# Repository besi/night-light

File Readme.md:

# NightLight

A simple night light to defy the nightly demons.

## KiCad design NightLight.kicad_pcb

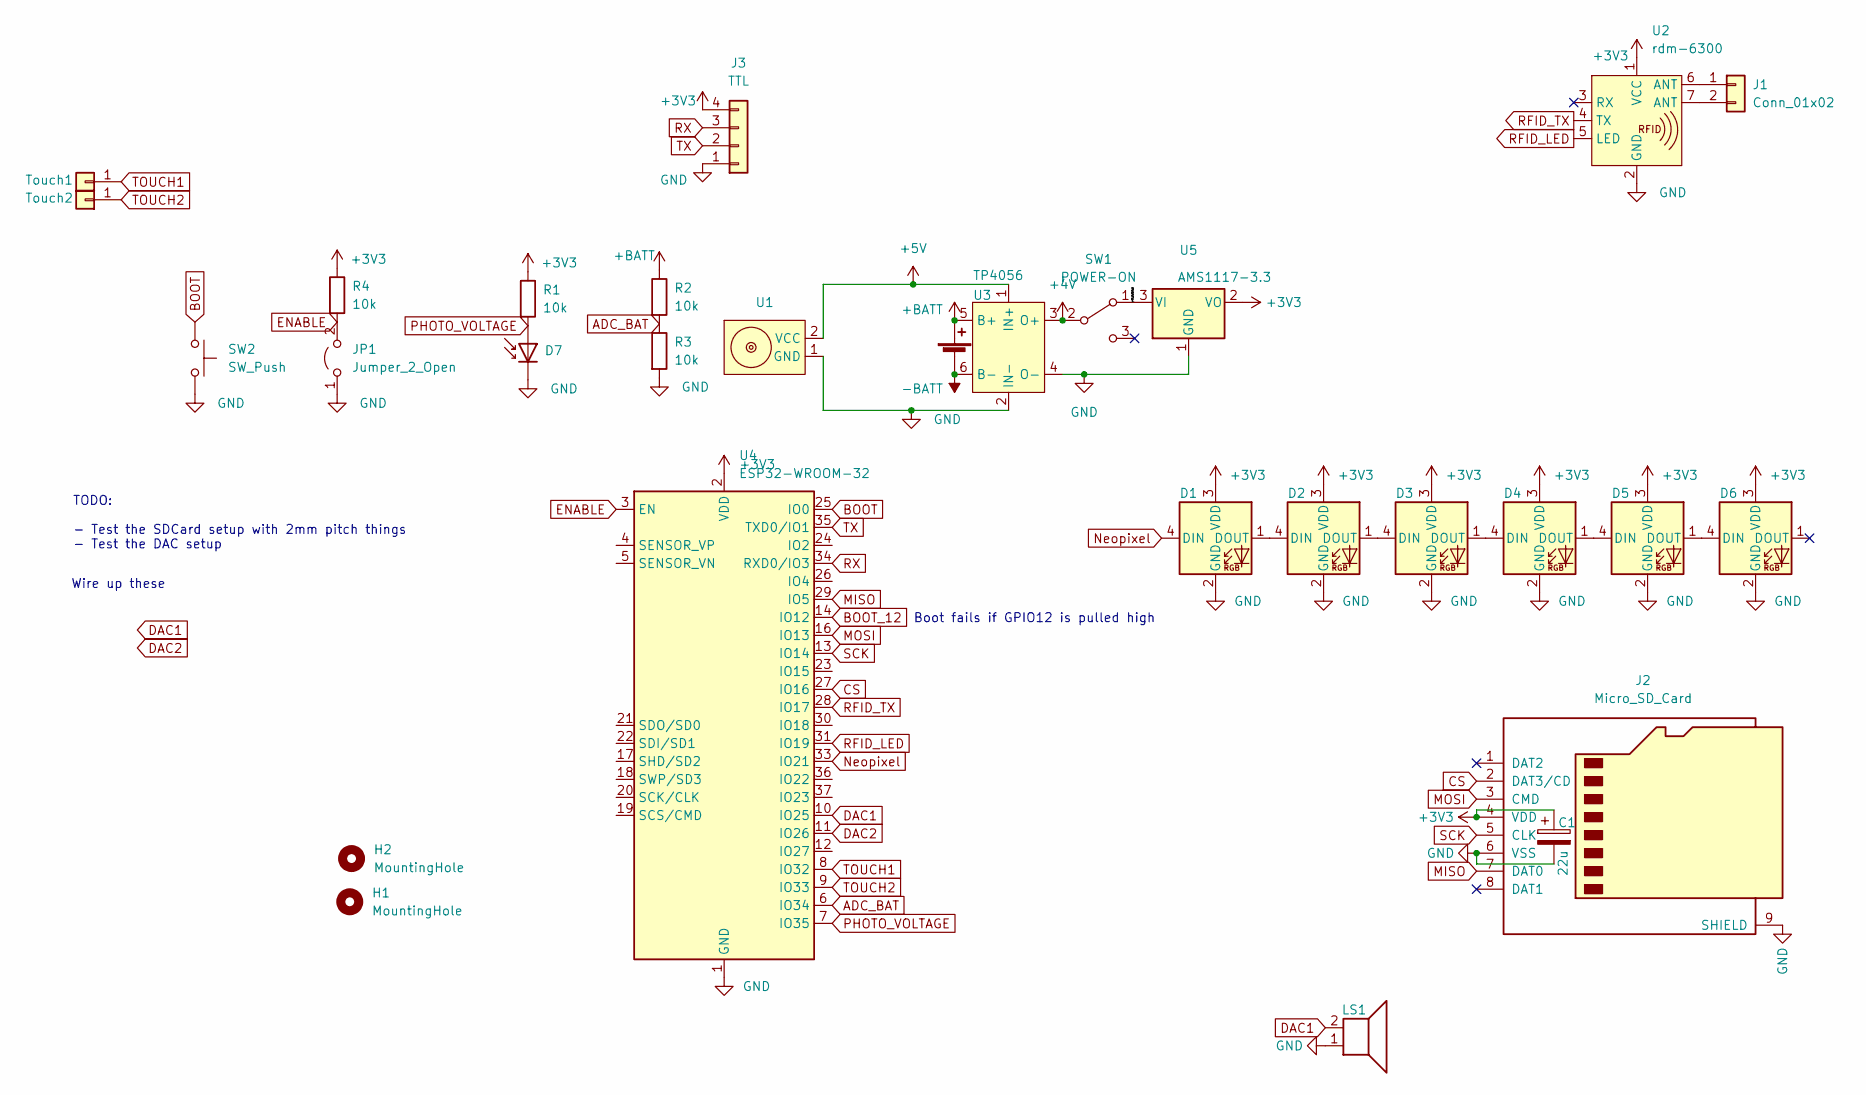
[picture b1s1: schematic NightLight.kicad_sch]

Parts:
BT1: Battery_Cell; JST_EH_S2B-EH_1x02_P2.50mm_Horizontal
C1: 22u; CP_Radial_D5.0mm_P2.50mm
D1, D2, D3, D4, D5, D6: NeoPixel_THT; LED_WS2812B_PLCC4_5.0x5.0mm_P3.2mm
D7: D_Photo; R_LDR_4.9x4.2mm_P2.54mm_Vertical
H1, H2: MountingHole; MountingHole_5.3mm_M5
J1: Conn_01x02; PinHeader_1x02_P2.54mm_Vertical
J2: Micro_SD_Card; sd-card
J3: TTL; PinHeader_1x04_P2.54mm_Vertical
J5: Touch1; PinHeader_1x01_P2.54mm_Vertical
J6: Touch2; PinHeader_1x01_P2.54mm_Vertical
JP1: Jumper_2_Open; PinHeader_1x02_P2.54mm_Vertical
LS1: Speaker; PinHeader_1x02_P2.54mm_Vertical
R1, R2, R3, R4: 10k; R_Axial_DIN0204_L3.6mm_D1.6mm_P5.08mm_Horizontal
SW1: POWER-ON; SW_SPDT_CK-JS102011SAQN
SW2: SW_Push; SW_PUSH_6mm_H4.3mm
U1: magnetic-charger
U2: rdm-6300
U3: TP4056
U4: ESP32-WROOM-32
U5: AMS1117-3.3; TO-252-2

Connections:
+3V3: C1.1, D1.3 (VDD), D2.3 (VDD), D3.3 (VDD), D4.3 (VDD), D5.3 (VDD), D6.3 (VDD), J2.4 (VDD), J3.4, R1.1, R4.1, U2.1 (VCC), U4.2 (VDD), U5.2 (VO)
+4V: SW1.2 (B), U3.3 (O+)
+5V: U1.2 (VCC), U3.1 (IN+)
+BATT: BT1.1 (+), R2.1, U3.5 (B+)
-BATT: BT1.2 (-), U3.6 (B-)
/+4V_Switched: SW1.1 (A), U5.3 (VI)
ADC_BAT: R2.2, R3.1, U4.6 (IO34)
BOOT: SW2.1, U4.25 (IO0)
BOOT_12: U4.14 (IO12)
CS: J2.2 (DAT3/CD), U4.27 (IO16)
DAC1: LS1.2, U4.10 (IO25)
DAC2: U4.11 (IO26)
ENABLE: JP1.2 (B), R4.2, U4.3 (EN)
GND: C1.2, D1.2 (GND), D2.2 (GND), D3.2 (GND), D4.2 (GND), D5.2 (GND), D6.2 (GND), D7.1 (K), J2.6 (VSS), J2.9 (SHIELD), J3.1, JP1.1 (A), LS1.1, R3.2, SW2.2, U1.1 (GND), U2.2 (GND), U3.2 (IN-), U3.4 (O-), U4.1 (GND), U4.15 (GND), U4.38 (GND), U4.39 (GND), U5.1 (GND)
MISO: J2.7 (DAT0), U4.29 (IO5)
MOSI: J2.3 (CMD), U4.16 (IO13)
Neopixel: D1.4 (DIN), U4.33 (IO21)
unnamed: D1.1 (DOUT), D2.4 (DIN)
unnamed: D2.1 (DOUT), D3.4 (DIN)
unnamed: D3.1 (DOUT), D4.4 (DIN)
unnamed: D4.1 (DOUT), D5.4 (DIN)
unnamed: D5.1 (DOUT), D6.4 (DIN)
unnamed: J1.1, U2.6 (ANT)
unnamed: J1.2, U2.7 (ANT)
PHOTO_VOLTAGE: D7.2 (A), R1.2, U4.7 (IO35)
RFID_LED: U2.5 (LED), U4.31 (IO19)
RFID_TX: U2.4 (TX), U4.28 (IO17)
RX: J3.3, U4.34 (RXD0/IO3)
SCK: J2.5 (CLK), U4.13 (IO14)
TOUCH1: J5.1, U4.8 (IO32)
TOUCH2: J6.1, U4.9 (IO33)
TX: J3.2, U4.35 (TXD0/IO1)

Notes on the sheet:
TODO: - Test the SDCard setup with 2mm pitch things - Test the DAC setup
Boot fails if GPIO12 is pulled high
Wire up these

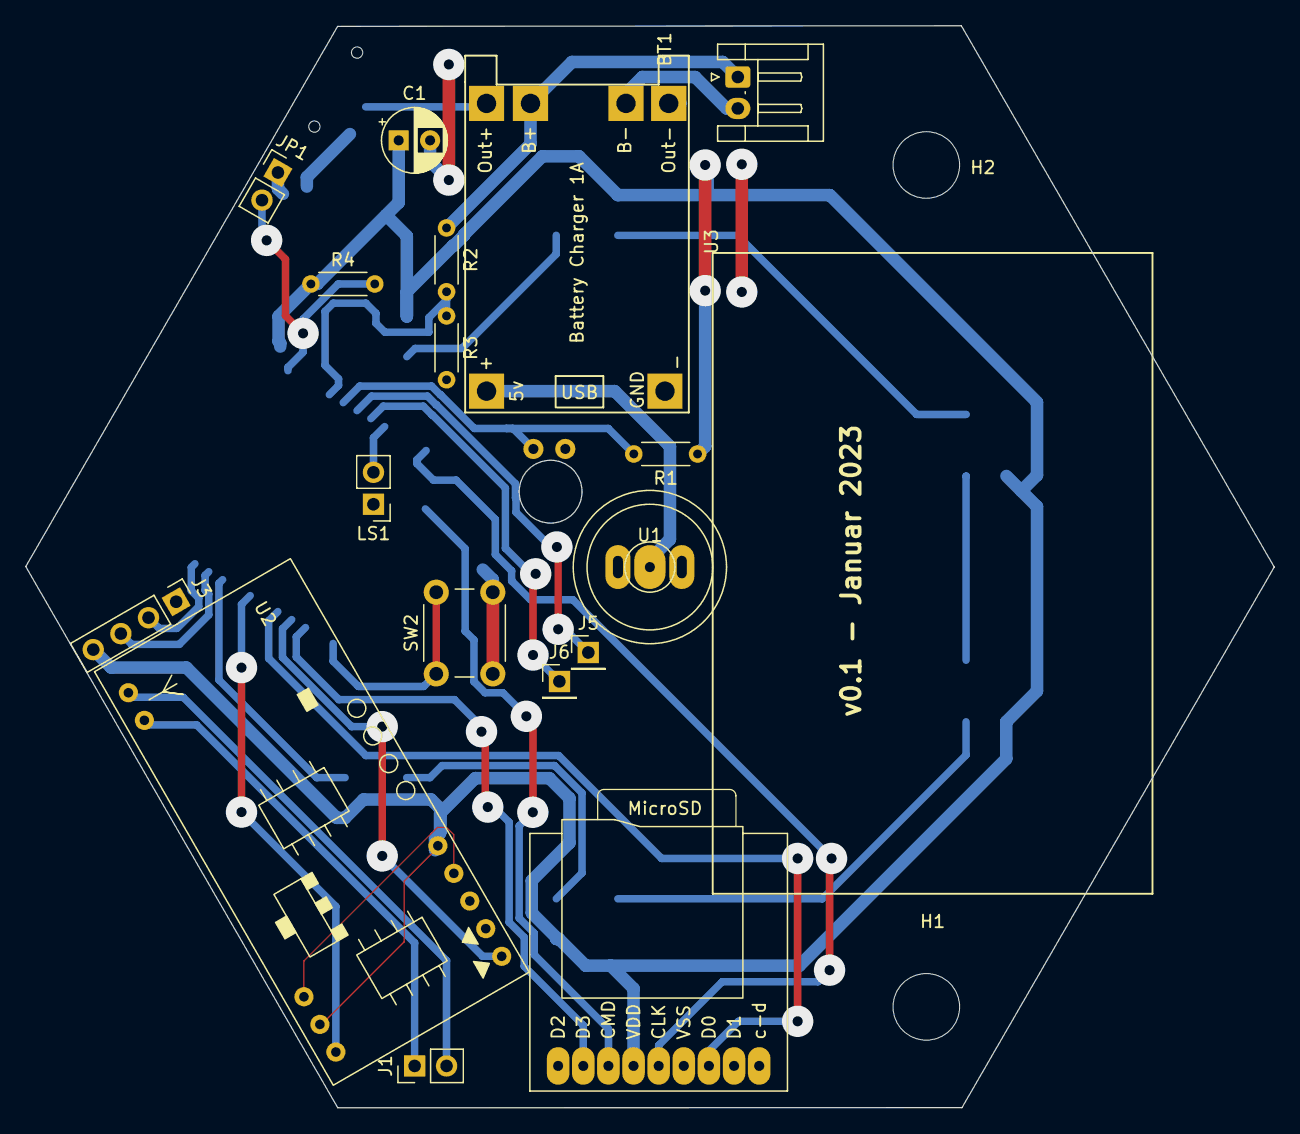
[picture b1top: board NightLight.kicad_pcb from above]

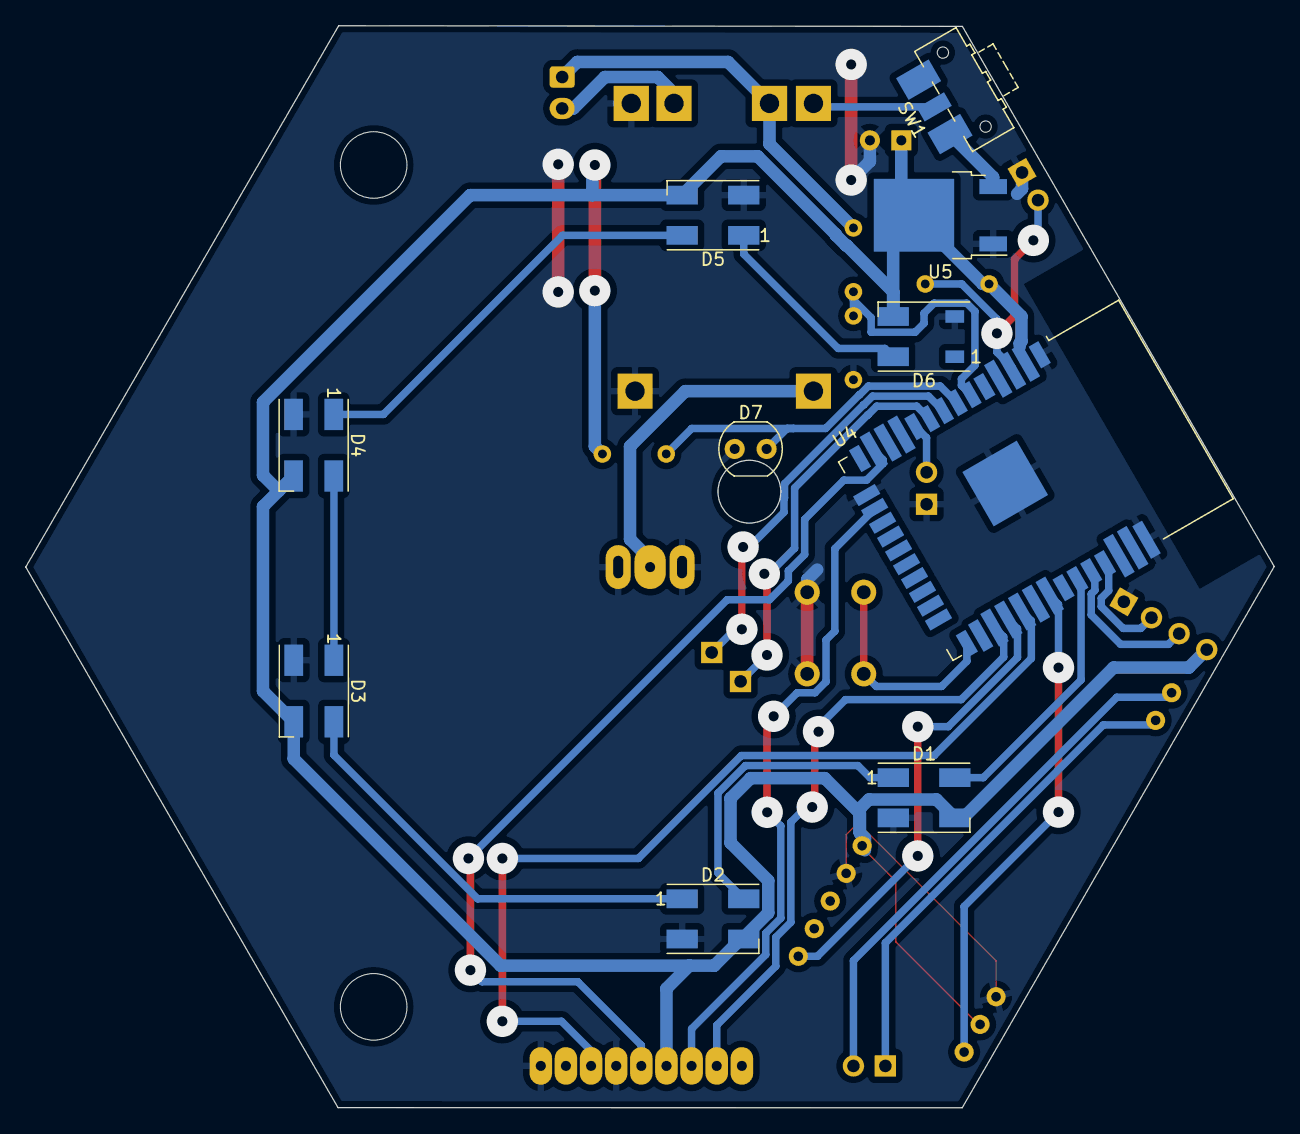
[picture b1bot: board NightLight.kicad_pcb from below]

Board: 2 copper layers, 99.4 x 86.1 mm, 29 parts (10 on the bottom side), 30 nets.

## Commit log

2023-01-12 Add sd card module
2023-01-12 Add lots of ocmponents
2023-01-13 Update magnetic charger footprint
2023-01-13 Add button and update the magnetic charger
2023-01-17 Updates from card board prototype
2023-01-20 Add version number
2023-02-14 Add a speaker outlet
2023-02-19 Minor changes
